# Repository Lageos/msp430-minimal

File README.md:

MSP430-Minimal
==============

* msp430-dsb18b20: Temperature Control, MSP430 board with DS18B20 as 2 Point Controler
* msp430-minimal-board: PCB layouts
* 

Project Page:
http://hackaday.io/project/3173-msp430-minimal

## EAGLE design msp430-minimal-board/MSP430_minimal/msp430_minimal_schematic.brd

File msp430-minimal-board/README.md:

MSP430-Minimal Board
==============

MSP430 board for MSP430 Value Line Microcontrolers

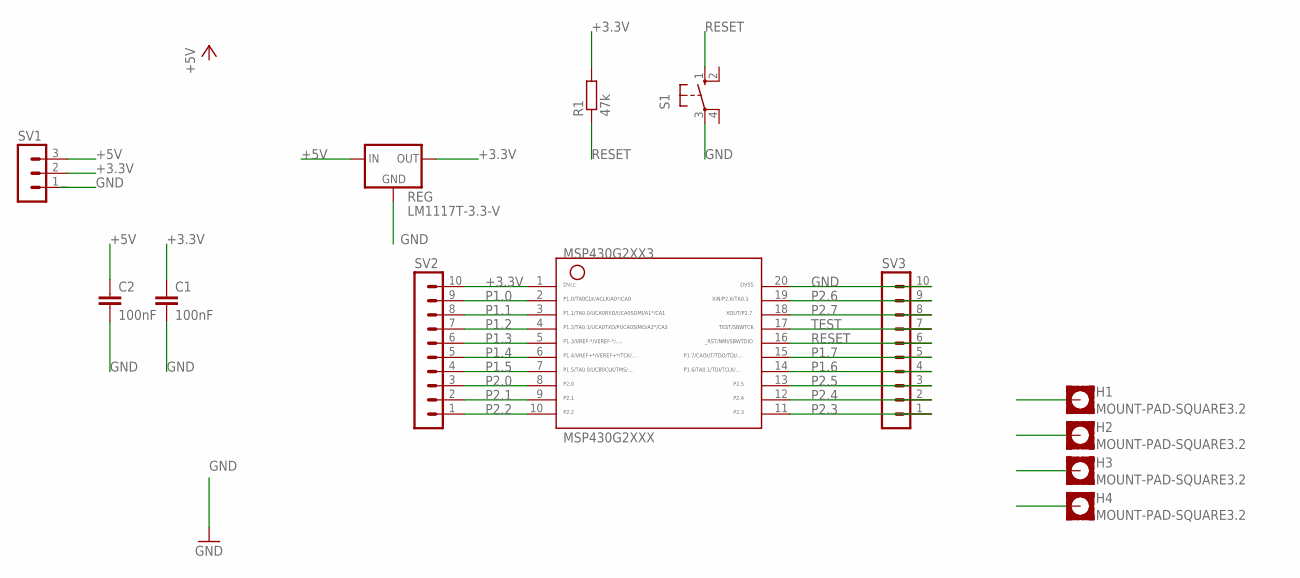
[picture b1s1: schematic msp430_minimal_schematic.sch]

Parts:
C1, C2: 100nF; C050-030X075
H1, H2, H3, H4: MOUNT-PAD-SQUARE3.2; 3,2-PAD-SQUARE
MSP430G2XXX: G2XX3---N20; N20
R1: 47k; 0204/7
REG: LM1117T-3.3-V; TO220V
S1: 10-XX; B3F-10XX
SV1: MA03-1
SV2, SV3: MA10-1

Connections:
+3.3V: C1.1, MSP430G2XXX.1, R1.2, REG.2 (OUT), SV1.2, SV2.10
+5V: C2.1, REG.3 (IN), SV1.3
GND: C1.2, C2.2, H1.B3,2, H2.B3,2, H3.B3,2, H4.B3,2, MSP430G2XXX.20, REG.1 (GND), S1.3, SV1.1, SV3.10
P1.0: MSP430G2XXX.2, SV2.9
P1.1: MSP430G2XXX.3, SV2.8
P1.2: MSP430G2XXX.4, SV2.7
P1.3: MSP430G2XXX.5, SV2.6
P1.4: MSP430G2XXX.6, SV2.5
P1.5: MSP430G2XXX.7, SV2.4
P1.6: MSP430G2XXX.14, SV3.4
P1.7: MSP430G2XXX.15, SV3.5
P2.0: MSP430G2XXX.8, SV2.3
P2.1: MSP430G2XXX.9, SV2.2
P2.2: MSP430G2XXX.10, SV2.1
P2.3: MSP430G2XXX.11, SV3.1
P2.4: MSP430G2XXX.12, SV3.2
P2.5: MSP430G2XXX.13, SV3.3
P2.6: MSP430G2XXX.19, SV3.9
P2.7: MSP430G2XXX.18, SV3.8
RESET: MSP430G2XXX.16, R1.1, S1.1 (S), SV3.6
TEST: MSP430G2XXX.17, SV3.7

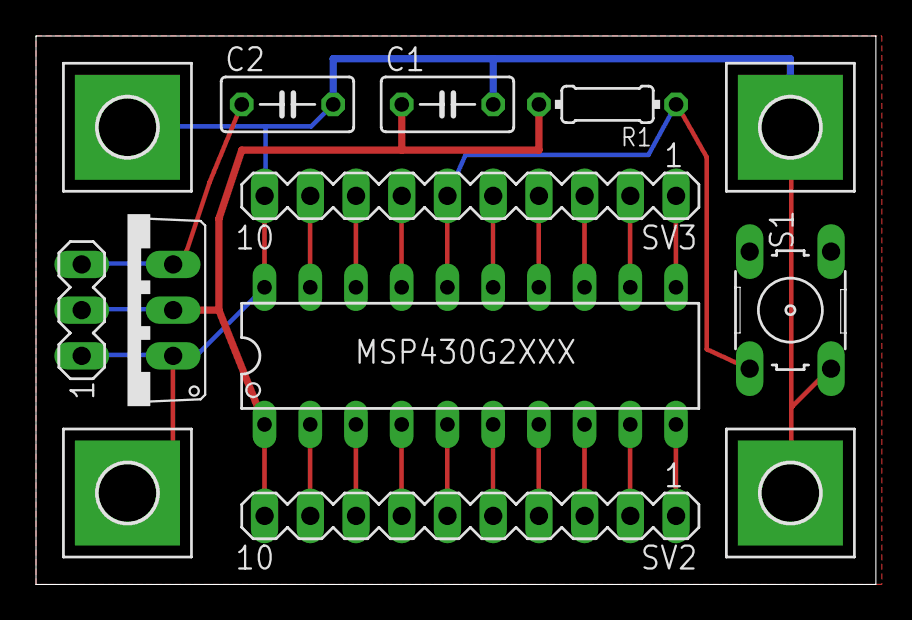
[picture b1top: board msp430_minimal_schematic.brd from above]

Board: 2 copper layers, 46.7 x 30.5 mm, 13 parts (0 on the bottom side), 21 nets.

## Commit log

2014-10-15 readme updates
2014-10-15 readme
2014-10-15 added eagle board
2014-10-15 board readme
2014-10-15 deleted unnecessary board
2014-10-15 gitignore eagle
2014-10-15 removed files
2014-10-15 new gitignore
2014-10-15 used new gitignore
2014-10-15 readme update
2014-10-15 interrupt
